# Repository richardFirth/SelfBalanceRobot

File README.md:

# SelfBalanceRobot

Self Balancing Robot Based on Joop Brokkings Model, Code, and BOM  

*CAD Model:* https://grabcad.com/library/self-balancing-robot-4  

His documentation is found here: http://www.brokking.net/yabr_main.html  

Joop's videos. These excellent videos taught me how to make this:  
Part 1:  https://www.youtube.com/watch?v=6WWqo-Yr8lA  
Part 2: https://www.youtube.com/watch?v=VxpMWncBKZc  
Part 3: https://www.youtube.com/watch?v=mG4OtAiY_wU  

I created a PCB for my own version of the project.  
My version uses an XBee in place of the bluetooth module,  
and the sparkfun wireless joystick instead of the nunchuck.  

I also connected the pins differently! The original code by Joop doesn't run on my copy.

*Joystick Code and Case:* https://github.com/richardFirth/WirelessJoystick  

Order PCB's in Model  
*Main PCB Board:* https://oshpark.com/shared_projects/zdu8sdQ4  
*Stepper Boards:* https://oshpark.com/shared_projects/qPz78o0H  (facilitate connection of stepper)

*Xbee Board:* https://oshpark.com/shared_projects/hA4cGipD  
(you need one of each to build the Robot)

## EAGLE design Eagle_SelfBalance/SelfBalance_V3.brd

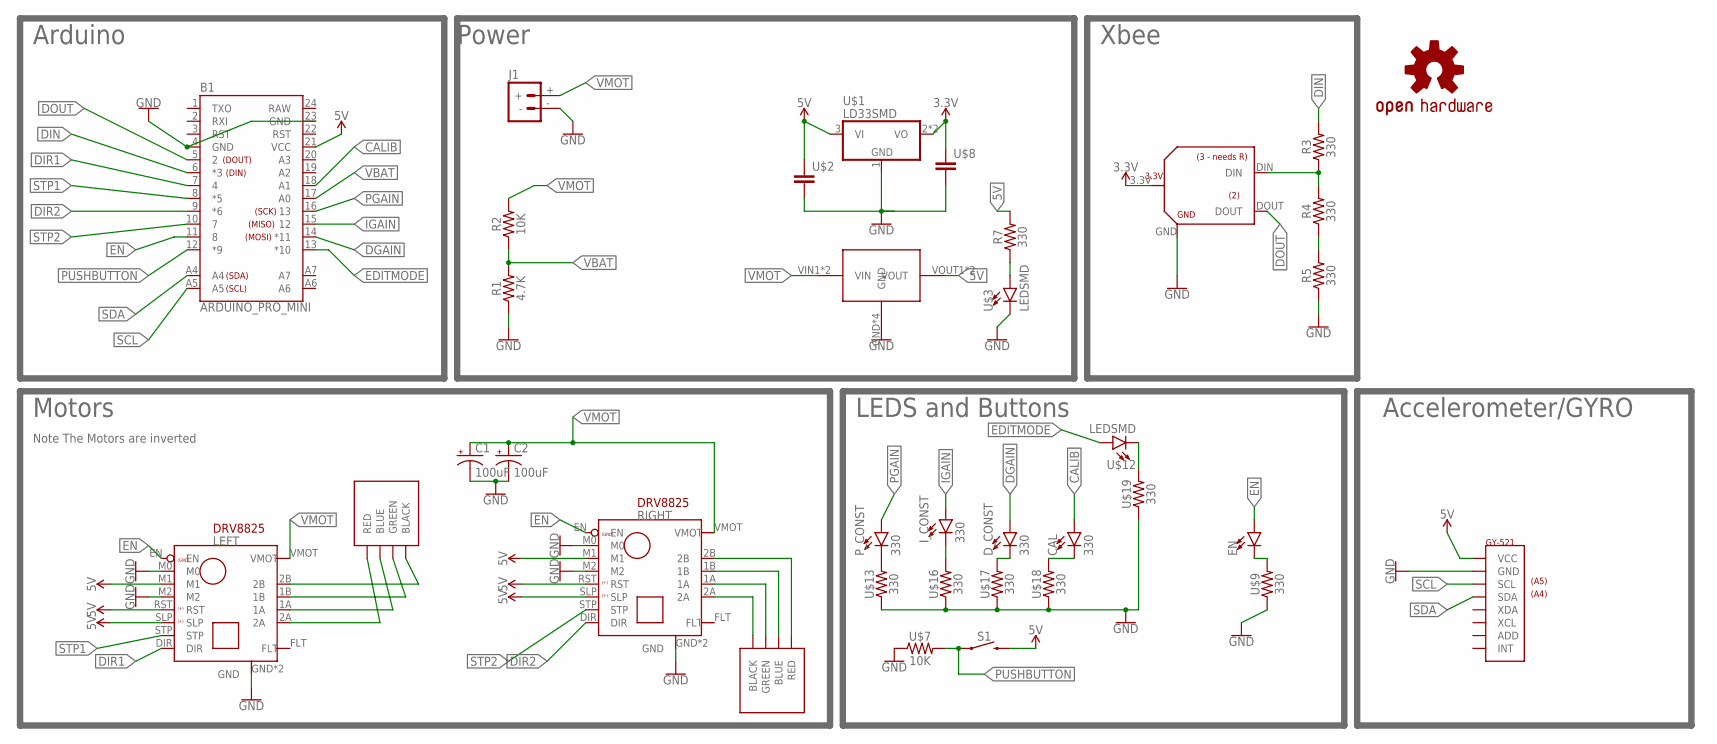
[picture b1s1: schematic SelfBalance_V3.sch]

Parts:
B1: ARDUINO_PRO_MINI
C1, C2: 100uF; CAP_E
CAL: 330; LED_SMD
D_CONST: 330; LED_SMD
EN: LEDSMD; LED_SMD
I_CONST: 330; LED_SMD
J1: BATTERY_CONNMALE; DEANS_MALE
LEFT: DRV8825
LOGO1: OSHW-LOGOL; OSHW-LOGO-L
P_CONST: 330; LED_SMD
R1: 4.7K; R1206
R2: 10K; R1206
R3, R4, R5, R7: 330; R1206
RIGHT: DRV8825
S1: PUSH_BUTTON6MM; BUTTON_6MM
U$1: LD33SMD; SOT223
U$2, U$8: CAP_SMCAP; C1206
U$3, U$12: LEDSMD; LED_SMD
U$4: STEPDOWNGREEN; STEPDOWN
U$5: GY-521
U$6: XBEE_BOUT
U$7: 10K; R1206
U$9, U$13, U$16, U$17, U$18, U$19: 330; R1206
U$14, U$15: STEPPER; 2X4

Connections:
3.3V: U$1.2 (VO), U$1.4 (VO), U$6.3.3V, U$8.1
5V: B1.21 (VCC), LEFT.M1, LEFT.RST, LEFT.SLP, R7.2, RIGHT.M1, RIGHT.RST, RIGHT.SLP, S1.3 (2), U$1.3 (VI), U$2.1, U$4.VOUT1 (VOUT), U$4.VOUT2 (VOUT), U$5.VCC
CALIB: B1.18 (A1), CAL.A
DGAIN: B1.14 (*11), D_CONST.A
DIN: B1.6 (*3), R3.2
DIR1: B1.7 (4), LEFT.DIR
DIR2: B1.9 (*6), RIGHT.DIR
DOUT: B1.5 (2), U$6.DOUT
EDITMODE: B1.13 (*10), U$12.A
EN: B1.11 (8), EN.A, LEFT.EN, RIGHT.EN
GND: B1.4 (GND), B1.23 (GND), C1.-, C2.-, J1.-, LEFT.GND, LEFT.GND2 (GND), LEFT.M0, LEFT.M2, R1.1, R5.1, RIGHT.GND, RIGHT.GND2 (GND), RIGHT.M0, RIGHT.M2, U$1.1 (GND), U$2.2, U$3.C, U$4.GND, U$4.GND2 (GND), U$4.GND3 (GND), U$4.GND4 (GND), U$5.GND, U$6.GND, U$7.1, U$8.2, U$9.1, U$13.1, U$16.1, U$17.1, U$18.1, U$19.1
IGAIN: B1.15 (12), I_CONST.A
unnamed: P_CONST.C, U$13.2
unnamed: LEFT.2B, U$14.B1 (BLACK), U$14.B2 (BLACK)
unnamed: R7.1, U$3.A
unnamed: I_CONST.C, U$16.2
unnamed: D_CONST.C, U$17.2
unnamed: CAL.C, U$18.2
unnamed: LEFT.1A, U$14.U1 (BLUE), U$14.U2 (BLUE)
unnamed: LEFT.2A, U$14.R1 (RED), U$14.R2 (RED)
unnamed: RIGHT.2B, U$15.R1 (RED), U$15.R2 (RED)
unnamed: RIGHT.1B, U$15.U1 (BLUE), U$15.U2 (BLUE)
unnamed: RIGHT.1A, U$15.G1 (GREEN), U$15.G2 (GREEN)
unnamed: RIGHT.2A, U$15.B1 (BLACK), U$15.B2 (BLACK)
unnamed: R4.1, R5.2
unnamed: R3.1, R4.2, U$6.DIN
unnamed: U$12.C, U$19.2
unnamed: EN.C, U$9.2
unnamed: LEFT.1B, U$14.G1 (GREEN), U$14.G2 (GREEN)
PGAIN: B1.16 (13), P_CONST.A
PUSHBUTTON: B1.12 (*9), S1.1, U$7.2
RAW: B1.24 (RAW)
SCL: B1.A5, U$5.SCL
SDA: B1.A4, U$5.SDA
STP1: B1.8 (*5), LEFT.STP
STP2: B1.10 (7), RIGHT.STP
VBAT: B1.17 (A0), R1.2, R2.1
VMOT: C1.+, C2.+, J1.+, LEFT.VMOT, R2.2, RIGHT.VMOT, U$4.VIN1 (VIN), U$4.VIN2 (VIN)

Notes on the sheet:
LEDS and Buttons
Motors
Arduino
Power
Xbee
Accelerometer/GYRO
Note The Motors are inverted

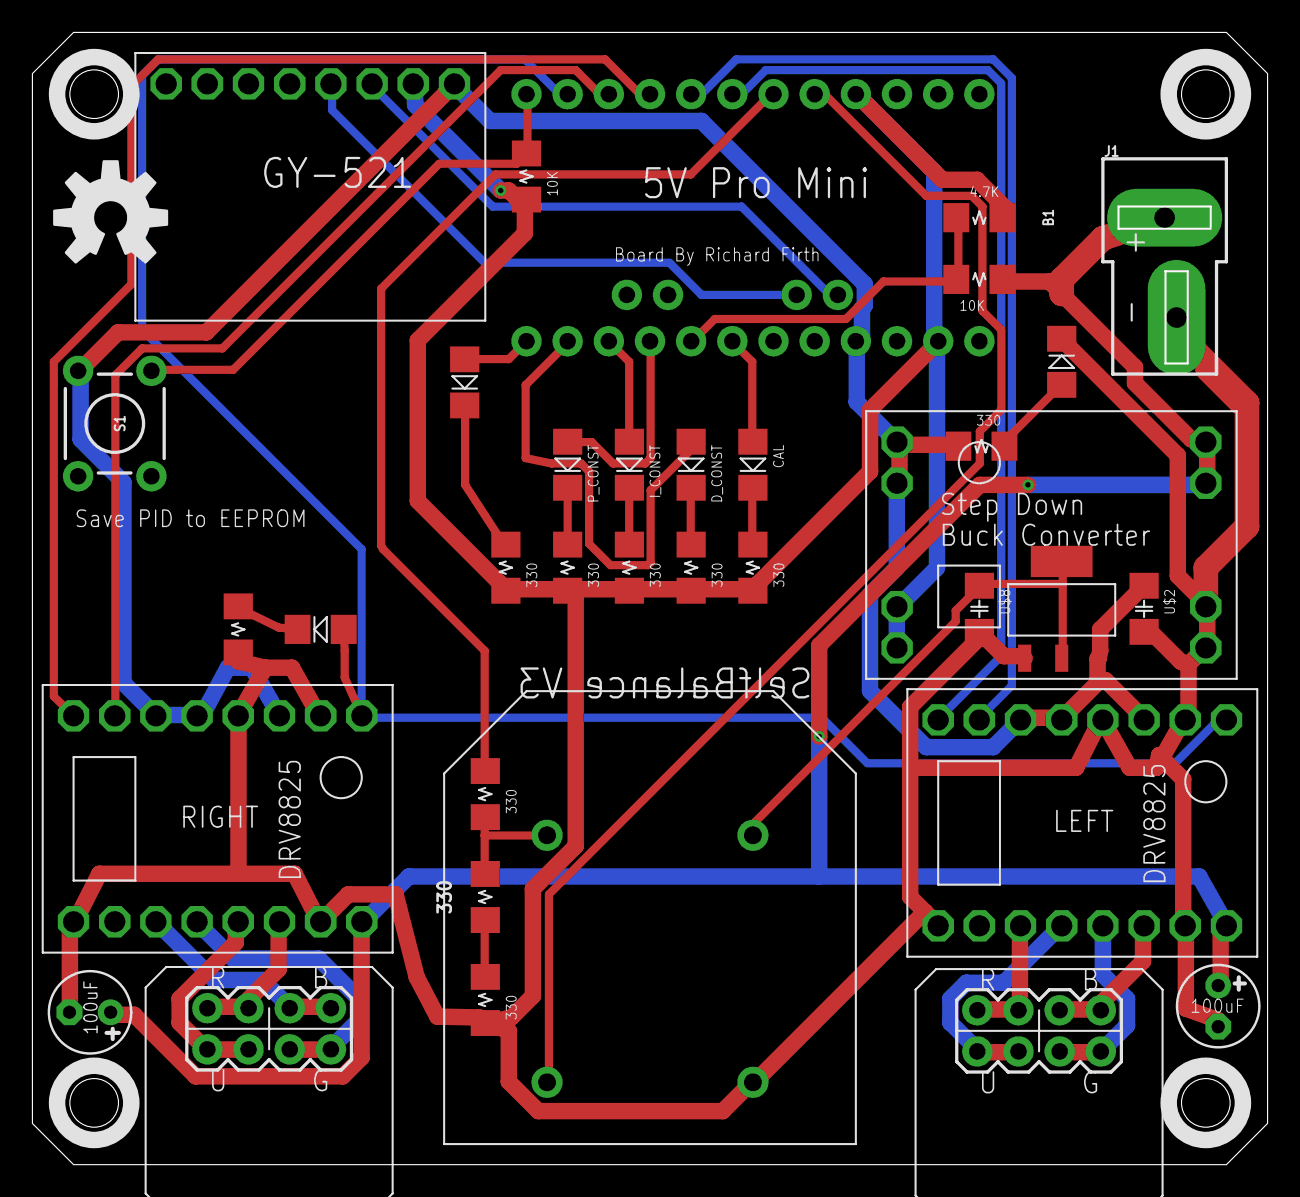
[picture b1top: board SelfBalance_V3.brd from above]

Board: 2 copper layers, 76.1 x 69.7 mm, 36 parts (0 on the bottom side), 37 nets.

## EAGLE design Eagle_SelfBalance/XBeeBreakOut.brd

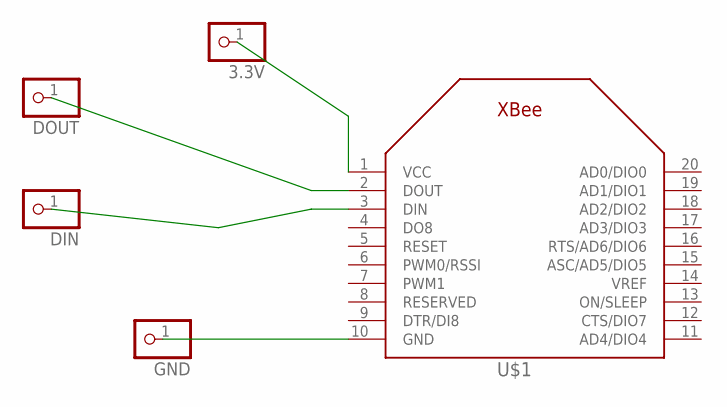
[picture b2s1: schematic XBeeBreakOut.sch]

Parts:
3.3V: PINHD-1X1; 1X01
DIN: PINHD-1X1; 1X01
DOUT: PINHD-1X1; 1X01
GND: PINHD-1X1; 1X01
U$1: XBEE

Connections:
DIN: DIN.1, U$1.3 (DIN)
DOUT: DOUT.1, U$1.2 (DOUT)
GND: GND.1, U$1.10 (GND)
VCC: 3.3V.1, U$1.1 (VCC)

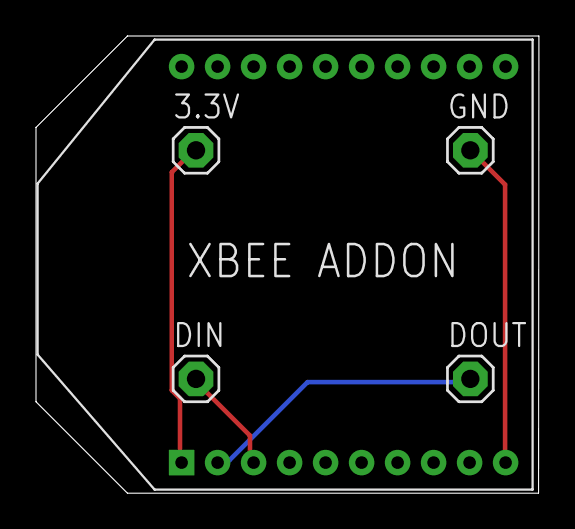
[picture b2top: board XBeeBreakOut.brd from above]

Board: 2 copper layers, 27.9 x 25.4 mm, 5 parts (0 on the bottom side), 4 nets.

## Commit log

2018-01-21 update ReadMe, add links, clean up documentation
2018-01-26 added eagle files, modified readme
2018-01-26 Add eagle PCB Files
    Eagle PCB files for self balancing robot based on Joops Video.
2018-01-28 Add DXF, update code to remove redundant functions
2018-02-16 Update README.md
    fix carridge return
2018-02-22 refactor to use SerialReceiver class

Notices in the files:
parts and their libraries:
SparkFun-Aesthetics: Licensing: Creative Commons ShareAlike 4.0 International - https://creativecommons.org/licenses/by-sa/4.0
